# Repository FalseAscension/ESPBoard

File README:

# ESPBoard

A breakout for the ESP-12E module with built-on flash and reset buttons, 3.3V Regulator and LED on GPIO 4.
See more on http://www.falseascension.xyz/ESPBoard/

    Copyright (C) 2016 FalseAscension

    This information is free: you can redistribute it and/or modify
    it under the terms of the GNU General Public License as published by
    the Free Software Foundation, either version 3 of the License, or
    (at your option) any later version.

    This work is distributed in the hope that it will be useful,
    but WITHOUT ANY WARRANTY; without even the implied warranty of
    MERCHANTABILITY or FITNESS FOR A PARTICULAR PURPOSE.  See the
    GNU General Public License for more details.

    You should have received a copy of the GNU General Public License
    along with this work.  If not, see <http://www.gnu.org/licenses/\>.

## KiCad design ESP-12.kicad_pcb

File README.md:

# ESPBoard

A breakout for the ESP-12E module with built-on flash and reset buttons.
Pullups on RESET, CH_PD, GPIO2, and GPIO0, a pulldown on GPIO15, along with
a switch attached to a pulldown on GPIO0 for flash mode and RESET.

    Copyright (C) 2016 FalseAscension

    This information is free: you can redistribute it and/or modify
    it under the terms of the GNU General Public License as published by
    the Free Software Foundation, either version 3 of the License, or
    (at your option) any later version.

    This work is distributed in the hope that it will be useful,
    but WITHOUT ANY WARRANTY; without even the implied warranty of
    MERCHANTABILITY or FITNESS FOR A PARTICULAR PURPOSE.  See the
    GNU General Public License for more details.

    You should have received a copy of the GNU General Public License
    along with this work.  If not, see <http://www.gnu.org/licenses/\>.

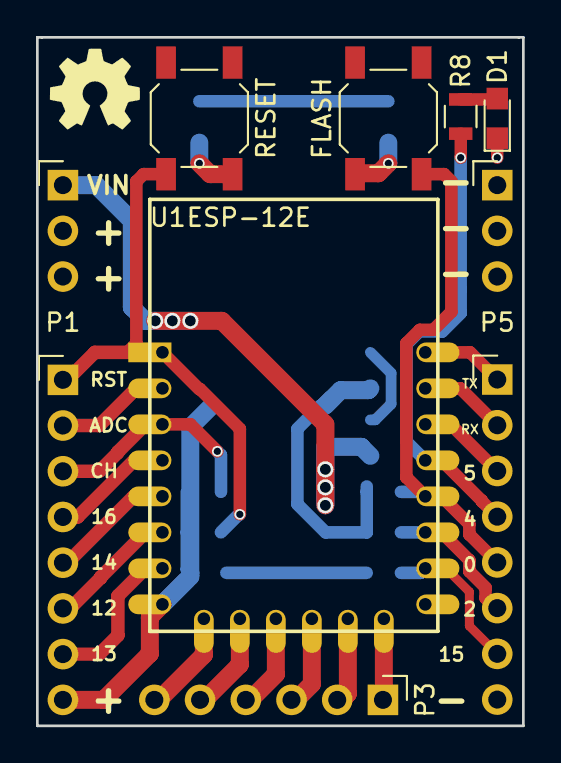
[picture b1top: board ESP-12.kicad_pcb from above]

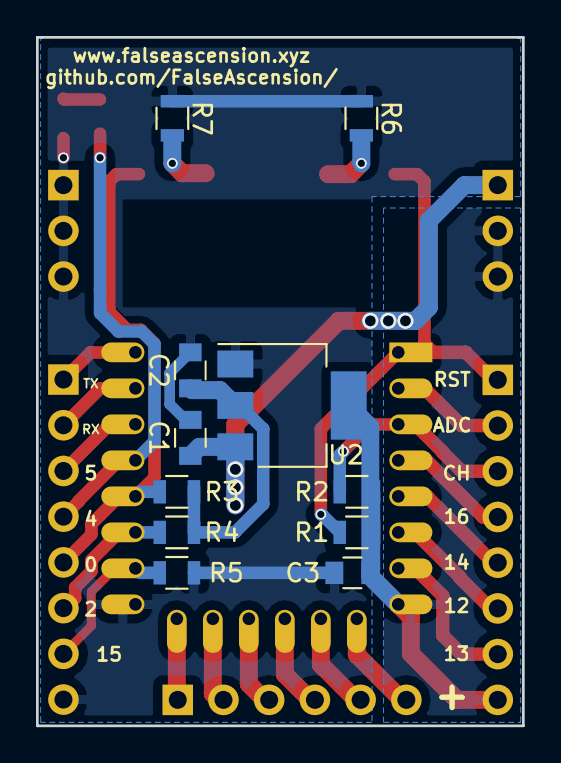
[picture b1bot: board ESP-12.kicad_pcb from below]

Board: 2 copper layers, 27.0 x 38.2 mm, 21 parts (11 on the bottom side), 26 nets.

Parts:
C1, C2: 10uF; C_0805
C3: 100nF; C_0805
D1: LED_0805
P1: VCC; Pin_Header_Straight_1x03_Pitch2.54mm
P2: GPIO_1; Pin_Header_Straight_1x08_Pitch2.54mm
P3: SPI; Pin_Header_Straight_1x06_Pitch2.54mm
P4: GPIO_2; Pin_Header_Straight_1x08_Pitch2.54mm
P5: GND; Pin_Header_Straight_1x03_Pitch2.54mm
R1, R2, R3, R4, R5, R6, R7: R; R_0805
R8: R_0805
SW1: FLASH; SW_SPST_SKQG
SW2: RESET; SW_SPST_SKQG
U1: ESP-12E; ESP-12E_TH
U2: AP1117-33; SOT-223-3Lead_TabPin2

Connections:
/ADC: P2.2, U1.2
/CH_PD: P2.3, R2.1, U1.3
/GPIO0: P4.5, R3.2, SW1.1, U1.12
/GPIO2: P4.6, R4.2, U1.11
/GPIO4: P4.4, R8.2, U1.13
/GPIO5: P4.3, U1.14
/GPIO9: P3.4, U1.19
/GPIO10: P3.3, U1.20
/GPIO12: P2.6, U1.6
/GPIO13: P2.7, U1.7
/GPIO14: P2.5, U1.5
/GPIO15: P4.7, R5.2, U1.10
/GPIO16: P2.4, U1.4
/MISO: P3.5, U1.18
/MOSI: P3.2, U1.21
/RST: P2.1, R1.1, SW2.1, U1.1
/RXD: P4.2, U1.15
/SCLK: P3.1, U1.22
/SS: P3.6, U1.17
/TXD: P4.1, U1.16
/VIN: C1.1, P1.1, U2.3
GND: C1.2, C2.2, C3.2, D1.1, P4.8, P5.1, P5.2, P5.3, R5.1, R6.1, R7.1, U1.9, U2.1
unnamed: D1.2, R8.1
unnamed: R6.2, SW2.2
unnamed: R7.2, SW1.2
VCC: C2.1, C3.1, P1.2, P1.3, P2.8, R1.2, R2.2, R3.1, R4.1, U1.8, U2.2

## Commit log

2016-08-07 Init
2016-08-13 License
2018-01-03 Regulator, LED, decreased width, + more
2018-02-19 Adjust pitch of power headers to match other headers
